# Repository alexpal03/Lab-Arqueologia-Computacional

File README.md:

# Lab-Arqueologia-Computacional

Repositorio dedicado a recopilar información y registrar avances sobre retrocomputadoras del Laboratorio de Arqueología Computacional

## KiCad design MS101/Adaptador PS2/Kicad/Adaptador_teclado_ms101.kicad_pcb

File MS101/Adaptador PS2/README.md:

# Interfaz de Teclado PS/2 a Protocolo Paralelo Microsistemas

Este proyecto implementa un conversor de hardware y software diseñado para leer eventos de un teclado estándar PS/2, interpretarlos, y traducirlos a un bus de datos paralelo de 8 bits propietario (estándar "Microsistemas"). 

El sistema gestiona la recepción asíncrona por interrupciones, decodifica los *scancodes* (incluyendo el estado de modificadores como Shift y Bloq Mayús), los traduce al estándar ASCII, y finalmente mapea dicho ASCII a la codificación binaria requerida por el hardware de destino.

## Nota:
Las teclas de funciones especiales y los shift no fueron nunca probados. Se presupone que el código funcionará. En todo caso, se debería preparar una disquetera para la MS101, correrle el sistema operativo, y luego probar que todas las funcionalidades se ejecuten correctamente.

---

## 🏗️ Arquitectura del Sistema

El flujo de procesamiento se divide en tres etapas principales:

1. **Capa Física (PS/2):** Lectura del protocolo serie síncrono mediante interrupciones de hardware.
2. **Capa Lógica (Máquina de estados):** Filtrado de *scancodes*, manejo de liberación de teclas (`0xF0`) y modificadores.
3. **Capa de Traducción (Pipeline):** `Scancode -> ASCII -> Binario Microsistemas -> Salida Paralela`.

---

## ⚡ 1. Protocolo PS/2 y Recepción por Hardware

El teclado PS/2 se comunica mediante dos líneas en configuración *Open-Drain* (Reloj y Datos). El microcontrolador actúa como receptor pasivo.

### Rutina de Interrupción (ISR)
La recepción se maneja en la función `PS2Interrupt()`, la cual está anclada al flanco de bajada (`FALLING`) del pin de reloj (`PS2_CLK`). 
El protocolo PS/2 envía tramas de **11 bits** por cada evento de teclado:
*   **1 bit de inicio** (siempre 0).
*   **8 bits de datos** (el *Scancode*, LSB primero).
*   **1 bit de paridad** (impar).
*   **1 bit de parada** (siempre 1).

La ISR ignora los bits de inicio, paridad y parada. Desplaza los 8 bits útiles hacia la variable `scancodeRecibido` usando bitwise (`scancodeRecibido |= (dataBit << (bitCount - 1))`). Al alcanzar los 11 bits, levanta la bandera `teclaLista` para cederle el control al bucle principal sin bloquear el procesador.

---

## 🧠 2. Procesamiento Lógico (Bucle Principal)

El `loop()` evalúa la bandera `teclaLista`. Si hay un scancode listo, pasa por una máquina de estados para determinar la acción correcta:

*   **Key Release (0xF0):** Los teclados PS/2 envían `0xF0` seguido del scancode de la tecla cuando esta se suelta. El código enciende la bandera `ignorarSiguienteByte` para no imprimir la letra dos veces. Si la tecla soltada es *Shift* (`0x12` o `0x59`), apaga la bandera `shiftPresionado`.
*   **Modificadores:** Si se presiona *Shift*, se enciende su bandera. Si se presiona *Bloq Mayús* (`0x58`), se invierte el estado booleano de `bloqMayuscActivado`.
*   **Gestión de Mayúsculas/Minúsculas:** Si se presiona una letra y el Bloq Mayús está activo, el sistema aplica aritmética de caracteres C++ (`ascii - 'a' + 'A'`) para invertir el *case* dinámicamente antes de la traducción final.

---

## 🔄 3. Pipeline de Tablas de Conversión

Una vez que se obtiene una tecla válida, atraviesa dos diccionarios de conversión:

1. **`SCANCODE_TO_ASCII_TABLE` (y versión Shifted):** Utiliza la estructura `std::map` para traducir el valor crudo del teclado a un código ASCII. Las teclas de función (F1-F11) están mapeadas intencionalmente a caracteres de control ASCII (0-31) no imprimibles (ej. F1 mapea a `US` [31]).
2. **`ASCII_TO_MICROSISTEMAS_TABLE`:** Es un *array* de 128 posiciones. Usa el valor ASCII obtenido como índice de acceso directo `[ascii]` (O(1)) para recuperar el byte final. 

El mapeo de Microsistemas tiene una estructura semántica en sus bits más significativos (MSB):
*   Los números inician con `0b10...`
*   Las mayúsculas inician con `0b11...`
*   Las minúsculas inician con `0b01...`

---

## 🔌 4. Salida de Hardware (Bus Paralelo)

El byte resultante (`codigoMicrosistemas`) se escribe en los pines GPIO. 
Se utiliza una máscara de bits `(codigoMicrosistemas & (1 << i))` dentro de un bucle `for` de 8 iteraciones para encender o apagar los pines definidos en el arreglo `DATA_PINS`.

Finalmente, se envía un pulso de validación (*Strobe*):
1.  Se levanta el pin `STB_PIN` a `HIGH`.
2.  Se aplica un retardo de `100 microsegundos` para cumplir con los tiempos de *setup/hold* del receptor.
3.  Se baja a `LOW`.

---

## 📊 Tabla de Mapeo Completa: Scancode a Microsistemas

A continuación se detalla el recorrido exacto de transformación de cada tecla, número y función desde el teclado físico hasta la salida binaria de 8 bits.

### 🔢 Números
| Scancode PS/2 (Hex) | ASCII Base (Char / Valor) | Tecla Microsistemas | Salida Binaria Microsistemas |
| :--- | :--- | :--- | :--- |
| **0x45** | `'0'` (48) | Número 0 | `0b10100000` |
| **0x16** | `'1'` (49) | Número 1 | `0b10100001` |
| **0x1E** | `'2'` (50) | Número 2 | `0b10100010` |
| **0x26** | `'3'` (51) | Número 3 | `0b10100011` |
| **0x25** | `'4'` (52) | Número 4 | `0b10100100` |
| **0x2E** | `'5'` (53) | Número 5 | `0b10100101` |
| **0x36** | `'6'` (54) | Número 6 | `0b10100110` |
| **0x3D** | `'7'` (55) | Número 7 | `0b10100111` |
| **0x3E** | `'8'` (56) | Número 8 | `0b10101000` |
| **0x46** | `'9'` (57) | Número 9 | `0b10101001` |

### 🔤 Letras Minúsculas
| Scancode PS/2 (Hex) | ASCII Base (Char / Valor) | Tecla Microsistemas | Salida Binaria Microsistemas |
| :--- | :--- | :--- | :--- |
| **0x1C** | `'a'` (97) | Letra a | `0b01110100` |
| **0x32** | `'b'` (98) | Letra b | `0b01111011` |
| **0x21** | `'c'` (99) | Letra c | `0b01111100` |
| **0x23** | `'d'` (100)| Letra d | `0b01111101` |
| **0x24** | `'e'` (101)| Letra e | `0b01111110` |
| **0x2B** | `'f'` (102)| Letra f | `0b01111111` |
| **0x34** | `'g'` (103)| Letra g | `0b01010110` |
| **0x33** | `'h'` (104)| Letra h | `0b01010111` |
| **0x43** | `'i'` (105)| Letra i | `0b01100010` |
| **0x3B** | `'j'` (106)| Letra j | `0b01100100` |
| **0x42** | `'k'` (107)| Letra k | `0b01100101` |
| **0x4B** | `'l'` (108)| Letra l | `0b01100110` |
| **0x3A** | `'m'` (109)| Letra m | `0b01100111` |
| **0x31** | `'n'` (110)| Letra n | `0b01011011` |
| **0x44** | `'o'` (111)| Letra o | `0b01100011` |
| **0x4D** | `'p'` (112)| Letra p | `0b01010100` |
| **0x15** | `'q'` (113)| Letra q | `0b01101010` |
| **0x2D** | `'r'` (114)| Letra r | `0b01010001` |
| **0x1B** | `'s'` (115)| Letra s | `0b01010101` |
| **0x2C** | `'t'` (116)| Letra t | `0b01010010` |
| **0x3C** | `'u'` (117)| Letra u | `0b01100001` |
| **0x2A** | `'v'` (118)| Letra v | `0b01011010` |
| **0x1D** | `'w'` (119)| Letra w | `0b01010000` |
| **0x22** | `'x'` (120)| Letra x | `0b01011001` |
| **0x35** | `'y'` (121)| Letra y | `0b01010011` |
| **0x1A** | `'z'` (122)| Letra z | `0b01011000` |

### 🅰️ Letras Mayúsculas (Requieren Modificador Shift / Bloq Mayús)
| Scancode PS/2 (Hex) | ASCII Shifted (Char / Valor) | Tecla Microsistemas | Salida Binaria Microsistemas |
| :--- | :--- | :--- | :--- |
| **0x1C** *(+ Shift)* | `'A'` (65) | Letra A | `0b11110100` |
| **0x32** *(+ Shift)* | `'B'` (66) | Letra B | `0b11111011` |
| **0x21** *(+ Shift)* | `'C'` (67) | Letra C | `0b11111100` |
| **0x23** *(+ Shift)* | `'D'` (68) | Letra D | `0b11111101` |
| **0x24** *(+ Shift)* | `'E'` (69) | Letra E | `0b11111110` |
| **0x2B** *(+ Shift)* | `'F'` (70) | Letra F | `0b11111111` |
| **0x34** *(+ Shift)* | `'G'` (71) | Letra G | `0b11010110` |
| **0x33** *(+ Shift)* | `'H'` (72) | Letra H | `0b11010111` |
| **0x43** *(+ Shift)* | `'I'` (73) | Letra I | `0b11100010` |
| **0x3B** *(+ Shift)* | `'J'` (74) | Letra J | `0b11100100` |
| **0x42** *(+ Shift)* | `'K'` (75) | Letra K | `0b11100101` |
| **0x4B** *(+ Shift)* | `'L'` (76) | Letra L | `0b11100110` |
| **0x3A** *(+ Shift)* | `'M'` (77) | Letra M | `0b11100111` |
| **0x31** *(+ Shift)* | `'N'` (78) | Letra N | `0b11011011` |
| **0x44** *(+ Shift)* | `'O'` (79) | Letra O | `0b11100011` |
| **0x4D** *(+ Shift)* | `'P'` (80) | Letra P | `0b11010100` |
| **0x15** *(+ Shift)* | `'Q'` (81) | Letra Q | `0b11101010` |
| **0x2D** *(+ Shift)* | `'R'` (82) | Letra R | `0b11010001` |
| **0x1B** *(+ Shift)* | `'S'` (83) | Letra S | `0b11010101` |
| **0x2C** *(+ Shift)* | `'T'` (84) | Letra T | `0b11010010` |
| **0x3C** *(+ Shift)* | `'U'` (85) | Letra U | `0b11100001` |
| **0x2A** *(+ Shift)* | `'V'` (86) | Letra V | `0b11011010` |
| **0x1D** *(+ Shift)* | `'W'` (87) | Letra W | `0b11010000` |
| **0x22** *(+ Shift)* | `'X'` (88) | Letra X | `0b11011001` |
| **0x35** *(+ Shift)* | `'Y'` (89) | Letra Y | `0b11010011` |
| **0x1A** *(+ Shift)* | `'Z'` (90) | Letra Z | `0b11011000` |

### 🛠️ Teclas de Control y Sistema
| Scancode PS/2 (Hex) | ASCII Base (Char / Valor) | Tecla / Acción Microsistemas | Salida Binaria Microsistemas |
| :--- | :--- | :--- | :--- |
| **0x29** | `SPACE` (32) | Espacio | `0b11011111` |
| **0x5A** (Enter) | `ETX` (3) | **SKIP** | `0b11011100` |
| **0x66** (Backspace) | `BS` (8) | **RESET** | `0b11110010` |
| **0x0D** (Tab)| `HT` (9) | **RIGHT ADJUST** | `0b11110101` |
| **0x76** (Escape)| `ESC` (27) | **NEW LINE** | `0b11110110` |
| **0x0A** (F8)| `DEL` (127) | **FIELD COR** | `0b11001000` |
| **0x05** (F1)| `US` (31) | **CHR BCK** | `0b11011110` |
| **0x06** (F2)| `GS` (29) | **FIELD BCK** | `0b11110000` |
| **0x04** (F3)| `RS` (30) | **REC BCK** | `0b11111000` |
| **0x0C** (F4)| `DC1` (17) | **CHR ADV** | `0b11001010` |
| **0x03** (F5)| `DC2` (18) | **FIELD ADV** | `0b11001100` |
| **0x0B** (F6)| `DC3` (19) | **REC ADV** | `0b11101100` |
| **0x83** (F7)| `BEL` (7) | **HEX** | `0b11000011` |
| **0x83** (F9)| `LF` (10) | **FUNC SEL** | `0b11000001` |
| **0x83** (F10)| `VT` (11) | **DUP** | `0b11001001` |
| **0x83** (F11)| `FF` (12) | **SEL PROG** | `0b11001101` |

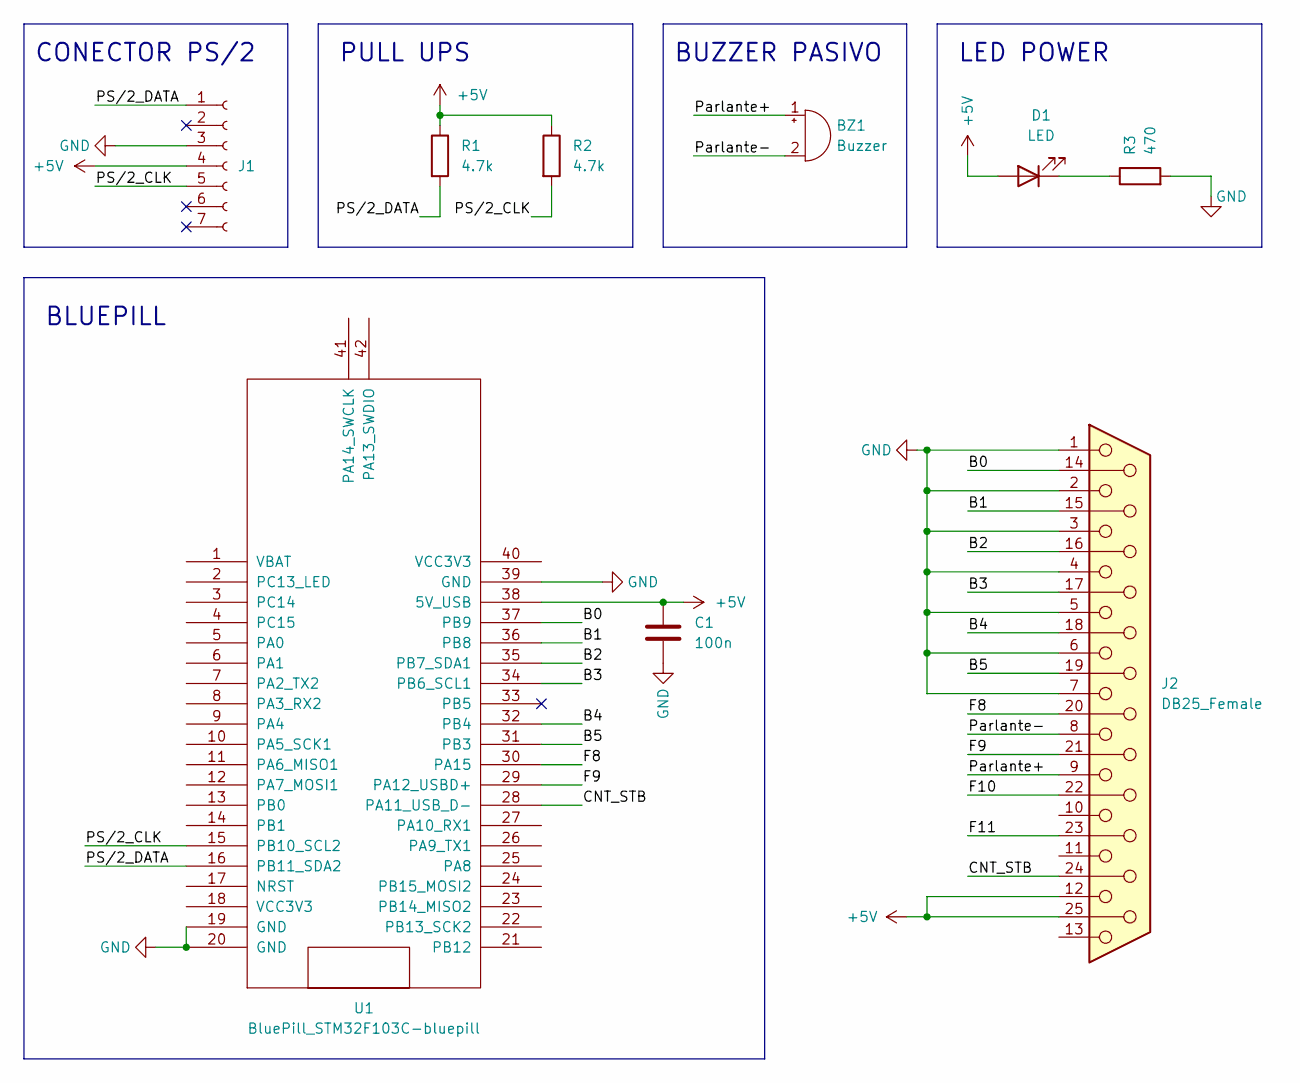
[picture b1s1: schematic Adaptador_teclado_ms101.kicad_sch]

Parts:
BZ1: Buzzer; Buzzer_12x9.5RM7.6
C1: 100n; C_Disc_D5.0mm_W2.5mm_P5.00mm
D1: LED; LED_D5.0mm
J1: Conn_01x07_Female; Connector_Mini-DIN_Female_6Pin_2rows
J2: DB25_Female; DSUB-25_Female_EdgeMount_P2.77mm
R1, R2: 4.7k; R_Axial_DIN0309_L9.0mm_D3.2mm_P12.70mm_Horizontal
R3: 470; R_Axial_DIN0309_L9.0mm_D3.2mm_P12.70mm_Horizontal
U1: BluePill_STM32F103C-bluepill; Bluepill

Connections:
+5V: C1.1, D1.2 (A), J1.4, J2.12, J2.25, R1.1, R2.1, U1.38 (5V_USB)
/B0: J2.14, U1.37 (PB9)
/B1: J2.15, U1.36 (PB8)
/B2: J2.16, U1.35 (PB7_SDA1)
/B3: J2.17, U1.34 (PB6_SCL1)
/B4: J2.18, U1.32 (PB4)
/B5: J2.19, U1.31 (PB3)
/CNT_STB: J2.24, U1.28 (PA11_USB_D-)
/F8: J2.20, U1.30 (PA15)
/F9: J2.21, U1.29 (PA12_USBD+)
/F10: J2.22
/F11: J2.23
/PS/2_CLK: J1.5, R2.2, U1.15 (PB10_SCL2)
/PS/2_DATA: J1.1, R1.2, U1.16 (PB11_SDA2)
/Parlante+: BZ1.1 (-), J2.9
/Parlante-: BZ1.2 (+), J2.8
GND: C1.2, J1.3, J2.1, J2.2, J2.3, J2.4, J2.5, J2.6, J2.7, R3.2, U1.19 (GND), U1.20 (GND), U1.39 (GND)
unnamed: D1.1 (K), R3.1

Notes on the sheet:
LED POWER
CONECTOR PS/2
BLUEPILL
PULL UPS
BUZZER PASIVO

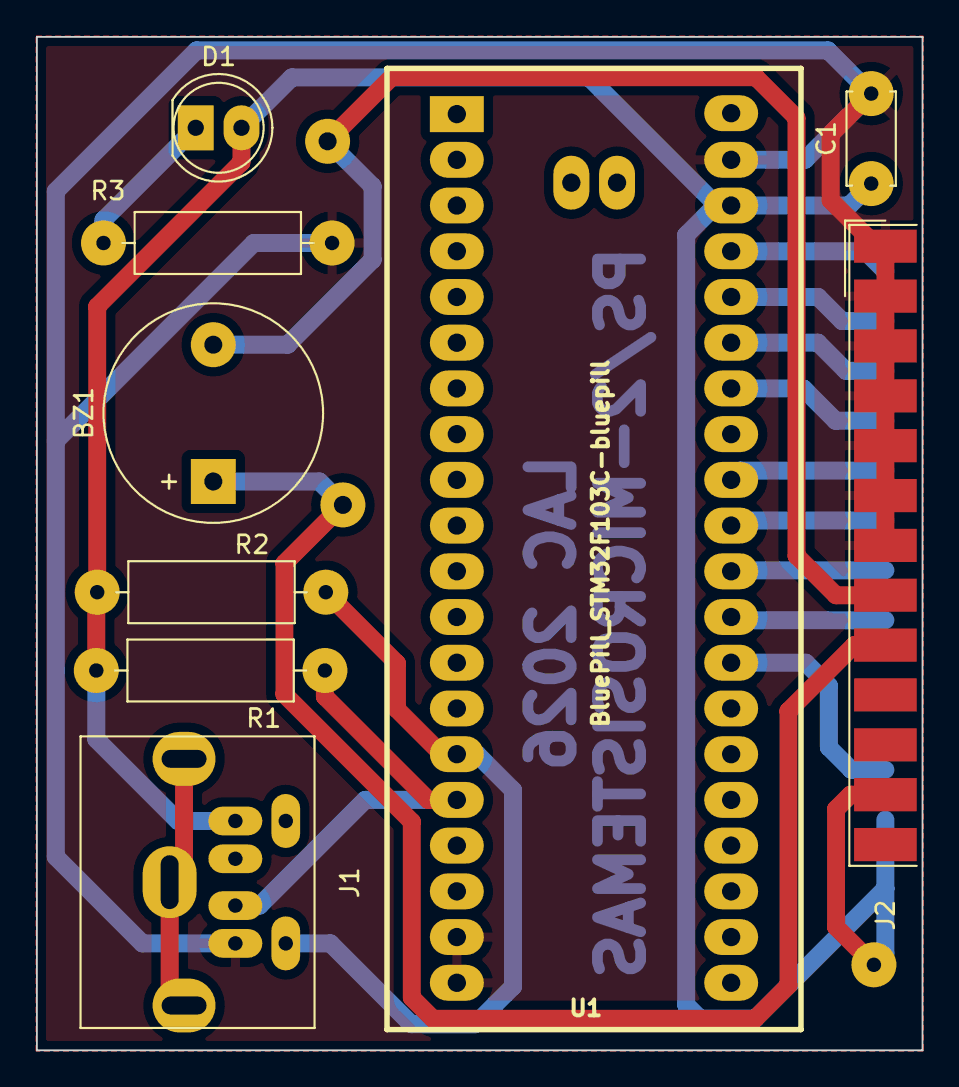
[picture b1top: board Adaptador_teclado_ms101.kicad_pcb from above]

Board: 2 copper layers, 49.2 x 56.3 mm, 9 parts (0 on the bottom side), 16 nets.

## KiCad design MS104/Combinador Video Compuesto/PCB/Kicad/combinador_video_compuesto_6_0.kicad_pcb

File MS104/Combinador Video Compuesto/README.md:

# Combinador Video Compuesto

## Principio de funcionamiento

La placa de video de las computadoras MS101 y MS104 funcionan generando 3 señales:

* Iluminación (3V)
* (VSYNC) Sincronización vertical de 50Hz (3.8V)
* (HSYNC) Sincronización Horizontal de 15.625Khz (3.65V)

La función de la placa combinadora es la de sumar las 3 señales para generar un video compuesto estandar PAL. Para poder lograrlo no solo hay que modificar las amplitudes de las señales, sino que tambien (en el caso de la sincronización horizontal) había que modificar su ancho de pulso. El objetivo era lograr una señal resultante de 1Vpp, que tenga la siguiente forma

Una parte clave del combinador era lograr que el pulso de HSYNC quede invertido, y con un ancho de pulso de 4.7us. Para ello, se utilizó un circuito RC temporizador que mediante regulación con un trimpot, modificaría la constante tau y permitiría ajustar a un ancho de 4.7us dejando la frecuencia intacta. Una vez conseguido esto, los valores de front porch y back porch se acomodaron solos.

Por otro lado, para el control del vertical, en el video compuesto tradicional se sustituye cada 20ms (50Hz) el pulso HSYNC por un pulso más largo, indicando que es momento de sincronizar el vertical. Esta sustitución se puede lograr mediante una operación lógica de AND entre el pulso horizontal y vertical. A esta señal resultante de la operación HSYNC & VSYNC se la conoce como CSYNC (Sincronización compuesta)

Una vez conseguido esto, solo es necesario sumar la señal CSYNC con la iluminación para obtener el video compuesto. La iluminación debe quedar con 0.7Vpp y el CSYNC con 0.3Vpp. Cabe aclarar que el transistor que se ocupa de realizar esta última suma debe ser un transistor de alta frecuencia, de lo contrario la señal de iluminación puede verse alterada. En esta placa se utilizó el [KPS10](https://www.alldatasheet.es/datasheet-pdf/pdf/53500/FAIRCHILD/KSP10.html)

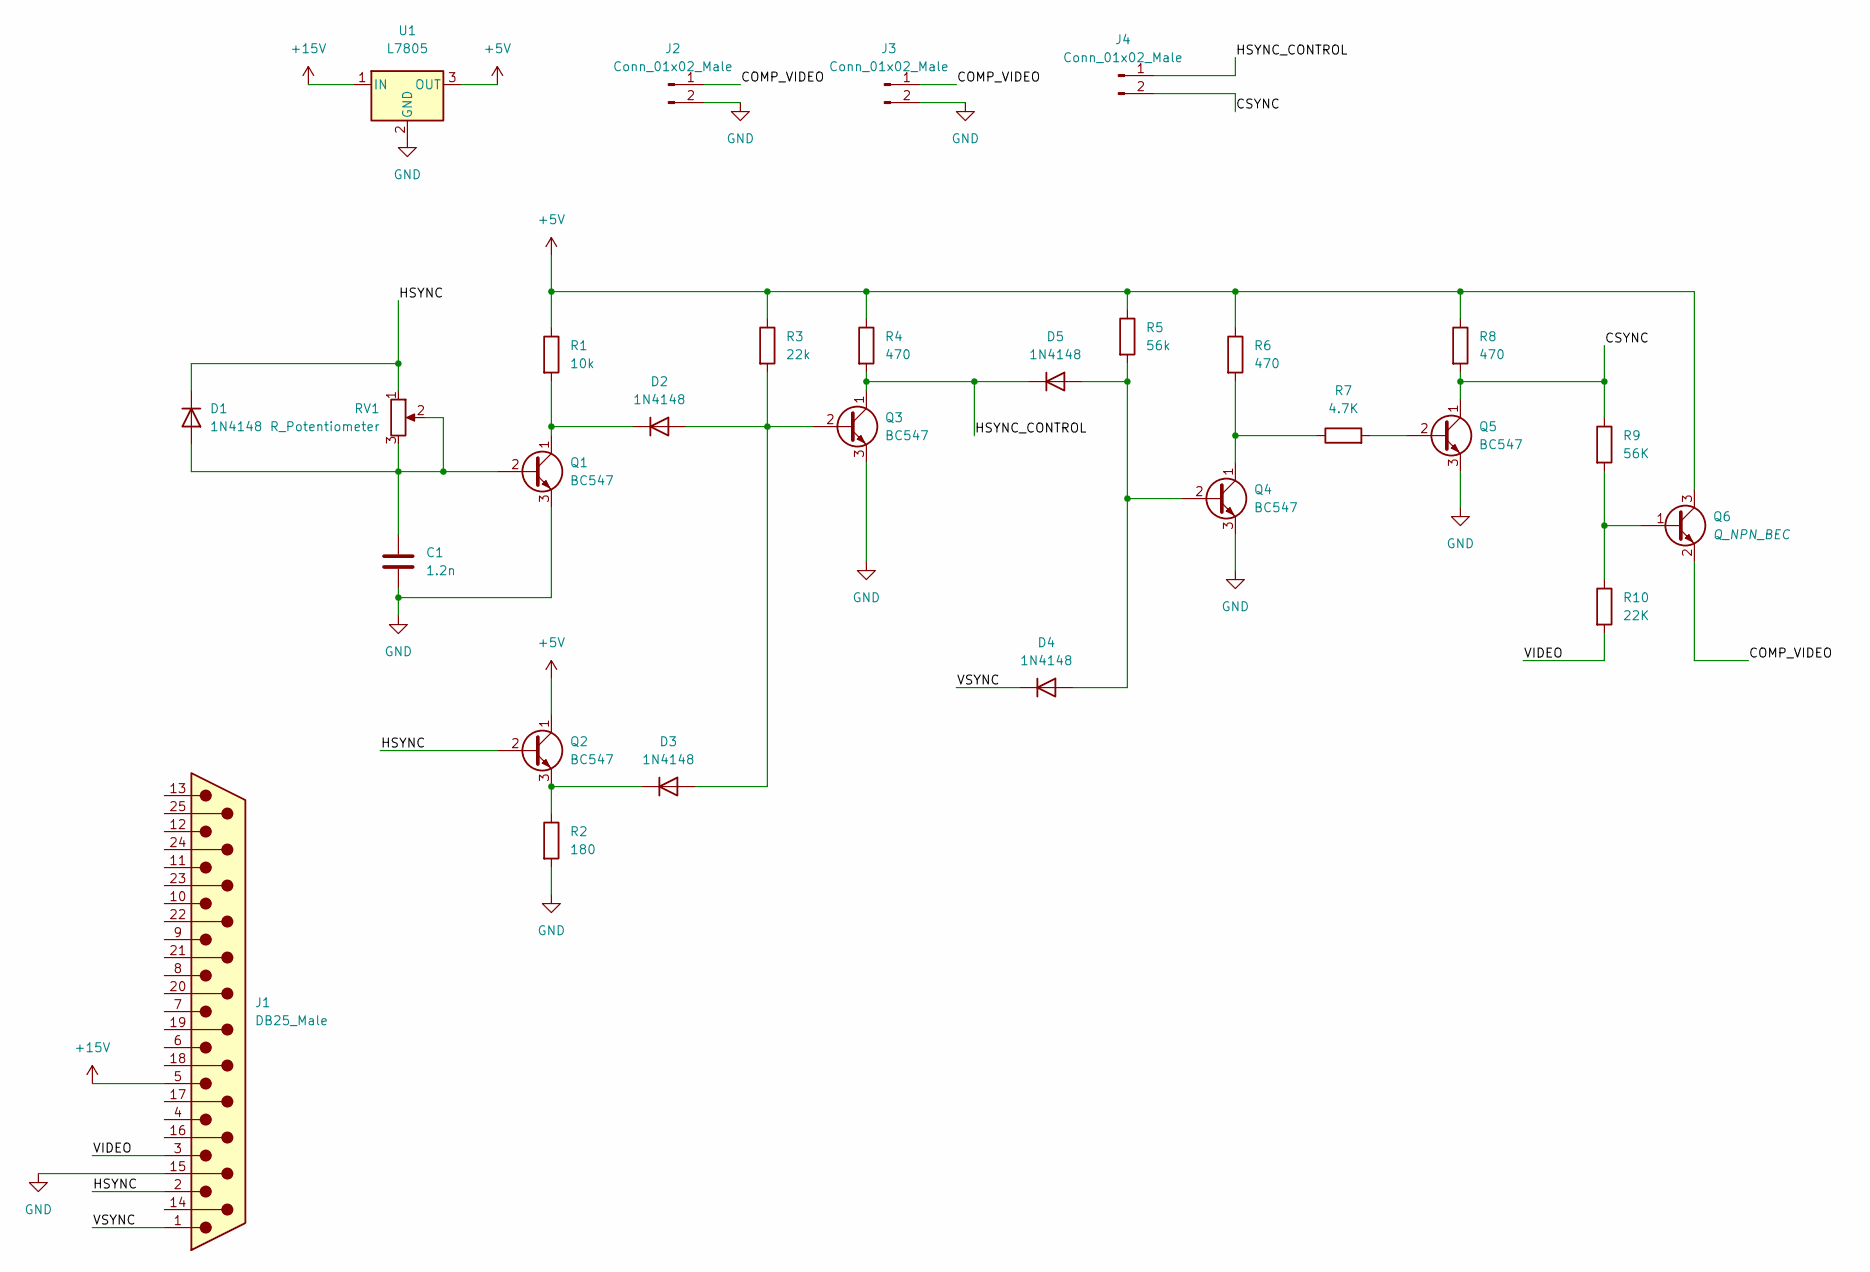
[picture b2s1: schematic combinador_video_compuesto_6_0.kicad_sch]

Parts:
C1: 1.2n; C_Disc_D7.5mm_W5.0mm_P5.00mm
D1, D2, D3, D4, D5: 1N4148; D_DO-35_SOD27_P7.62mm_Horizontal
J1: DB25_Male; DSUB-25_Male_EdgeMount_P2.77mm
J2: Conn_01x02_Male; PinHeader_1x02_P2.54mm_Horizontal
J3: Conn_01x02_Male; BNC_Amphenol_B6252HB-NPP3G-50_Horizontal
J4: Conn_01x02_Male; PinHeader_1x02_P2.54mm_Vertical
Q1, Q2, Q3, Q4, Q5: BC547; TO-92_Wide
Q6: Q_NPN_BEC; TO-92_Wide
R1: 10k; R_Axial_DIN0411_L9.9mm_D3.6mm_P12.70mm_Horizontal
R2: 180; R_Axial_DIN0411_L9.9mm_D3.6mm_P12.70mm_Horizontal
R3: 22k; R_Axial_DIN0411_L9.9mm_D3.6mm_P12.70mm_Horizontal
R4, R6, R8: 470; R_Axial_DIN0411_L9.9mm_D3.6mm_P12.70mm_Horizontal
R5: 56k; R_Axial_DIN0411_L9.9mm_D3.6mm_P12.70mm_Horizontal
R7: 4.7K; R_Axial_DIN0411_L9.9mm_D3.6mm_P12.70mm_Horizontal
R9: 56K; R_Axial_DIN0411_L9.9mm_D3.6mm_P12.70mm_Horizontal
R10: 22K; R_Axial_DIN0411_L9.9mm_D3.6mm_P12.70mm_Horizontal
RV1: R_Potentiometer; Potentiometer_Bourns_3006P_Horizontal
U1: L7805; TO-220-3_Vertical

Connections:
+5V: Q2.1 (C), Q6.3 (C), R1.1, R3.1, R4.1, R5.1, R6.1, R8.1, U1.3 (OUT)
+15V: J1.5, U1.1 (IN)
/COMP_VIDEO: J2.1, J3.1, Q6.2 (E)
/CSYNC: J4.2, Q5.1 (C), R8.2, R9.1
/HSYNC: D1.1 (K), J1.2, Q2.2 (B), RV1.1
/HSYNC_CONTROL: D5.1 (K), J4.1, Q3.1 (C), R4.2
/VIDEO: J1.3, R10.2
/VSYNC: D4.1 (K), J1.1
GND: C1.2, J1.15, J2.2, J3.2, Q1.3 (E), Q3.3 (E), Q4.3 (E), Q5.3 (E), R2.2, U1.2 (GND)
unnamed: C1.1, D1.2 (A), Q1.2 (B), RV1.2, RV1.3
unnamed: D2.1 (K), Q1.1 (C), R1.2
unnamed: D2.2 (A), D3.2 (A), Q3.2 (B), R3.2
unnamed: D3.1 (K), Q2.3 (E), R2.1
unnamed: D4.2 (A), D5.2 (A), Q4.2 (B), R5.2
unnamed: Q4.1 (C), R6.2, R7.1
unnamed: Q5.2 (B), R7.2
unnamed: Q6.1 (B), R9.2, R10.1

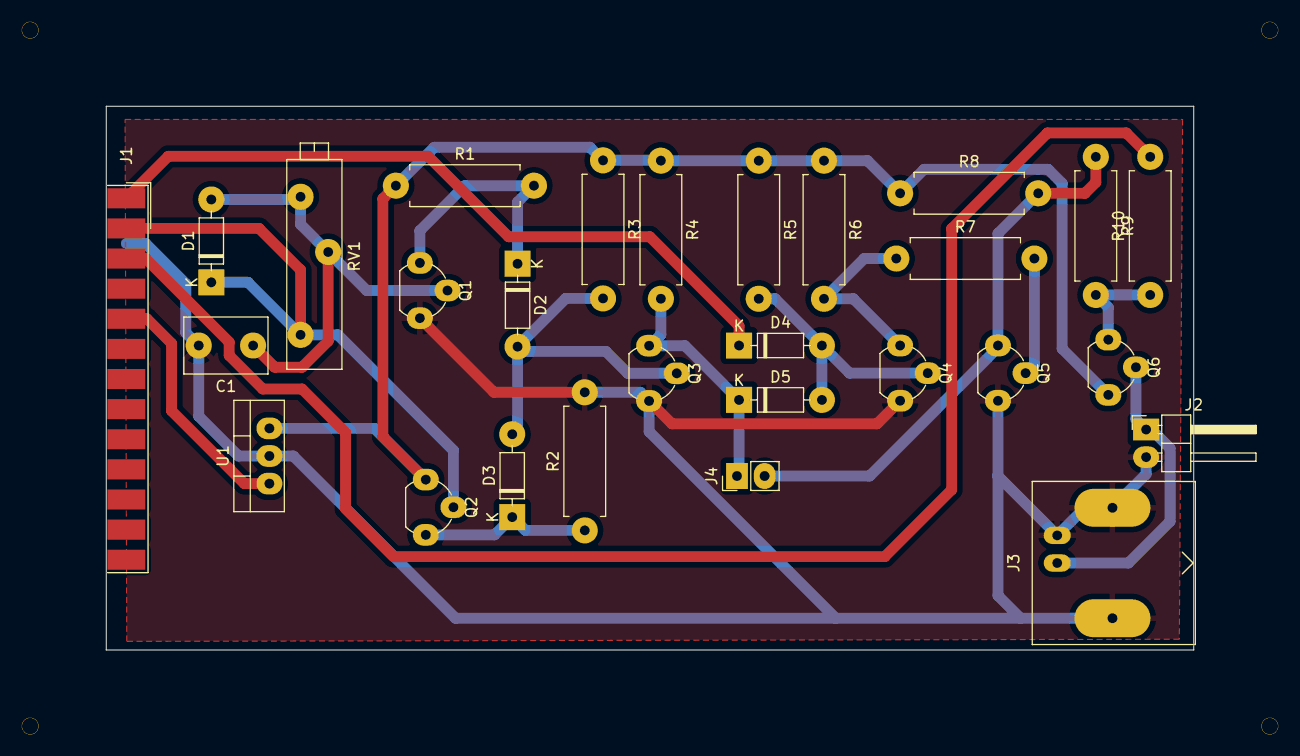
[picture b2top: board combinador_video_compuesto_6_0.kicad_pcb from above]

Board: 2 copper layers, 100.0 x 50.0 mm, 28 parts (0 on the bottom side), 17 nets.

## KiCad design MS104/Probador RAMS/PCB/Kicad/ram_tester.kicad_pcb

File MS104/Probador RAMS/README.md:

# Probador de RAM de 64kbytes para MS101 - MS104

El probador tiene capacidad de verificar hasta 64kbytes de memoria RAM, pero lo hace por sectores conformados por 8kbytes.
En total hay 8 sectores.

La decisión de usar esta delimitación de sectores es debido al mapeo de memoria de la 101-104:

|Sector| Direcciones |
| ---- | --------- |
|  I   |0000 - 1FFF|
|  II (A)   |2000 - 3FFF|
| III (B)  |4000 - 5FFF|
|  IV   |6000 - 7FFF|
|  V (C)  |8000 - 9FFF|
|  VI   |A000 - BFFF|
|  VII   |C000 - DFFF|
|  VIII (D)  |E000 - FFFF|

## Modo de uso

1. Conectar el probador de ram en el algún espacio del rack de tarjetas, preferiblemene en el espacio del CPU. Desconectar todas las demás placas, menos la tarjeta RAM
2. Hacer doble click en el botón para entrar a la configuración, donde se podrá seleccionar el sector a testear. Para moverse por las opciones se debe hacer un solo click, y una vez que se seleccione el sector deseado se vuelve a presionar doble click para volver al inicio.
3. Una vez en el inicio, se comienza el test con un solo click.
4. Al finalizar el test, aparece la primera pantalla de resultado, que indica la cantidad de direcciones donde hubo errores de lectura. Con un click se pasa a la siguiente pantalla, donde se muestra con mayor detalle los bits que tuvieron fallas organizados en bloques de 1kbyte. Ejemplo:

    ```
    7F 00 00 00
    00 50 00 00
    ```
    El `7F` que en binario es `01111111`, significa que en el primer bloque de 1kbyte fallaron todos los bits a excepción del más significativo.
    El `50` que en binario es `01010000` significa que en el sexto bloque de 1kbyte solo hay fallas en el B6 y B4.

    Esta subdivisión es útil porque tanto los integrados de RAM de la 101 y la 104 son de 1024 direcciones. De esta forma se puede localizar mucho más fácil la falla. Ej: si todos los bloques de 1kbyte fallan en el mismo bit, es probable que la falla sea del buffer de datos, y no de las RAM.

   A continuación se muestra un mapa de memoria de la MS104 y como se deben interpŕetar los resultados en el mapa

[Con mas detalle en este link](https://github.com/alexpal03/Lab-Arqueologia-Computacional/blob/main/MS104/Probador%20RAMS/Lectura%20de%20resultados.pdf)

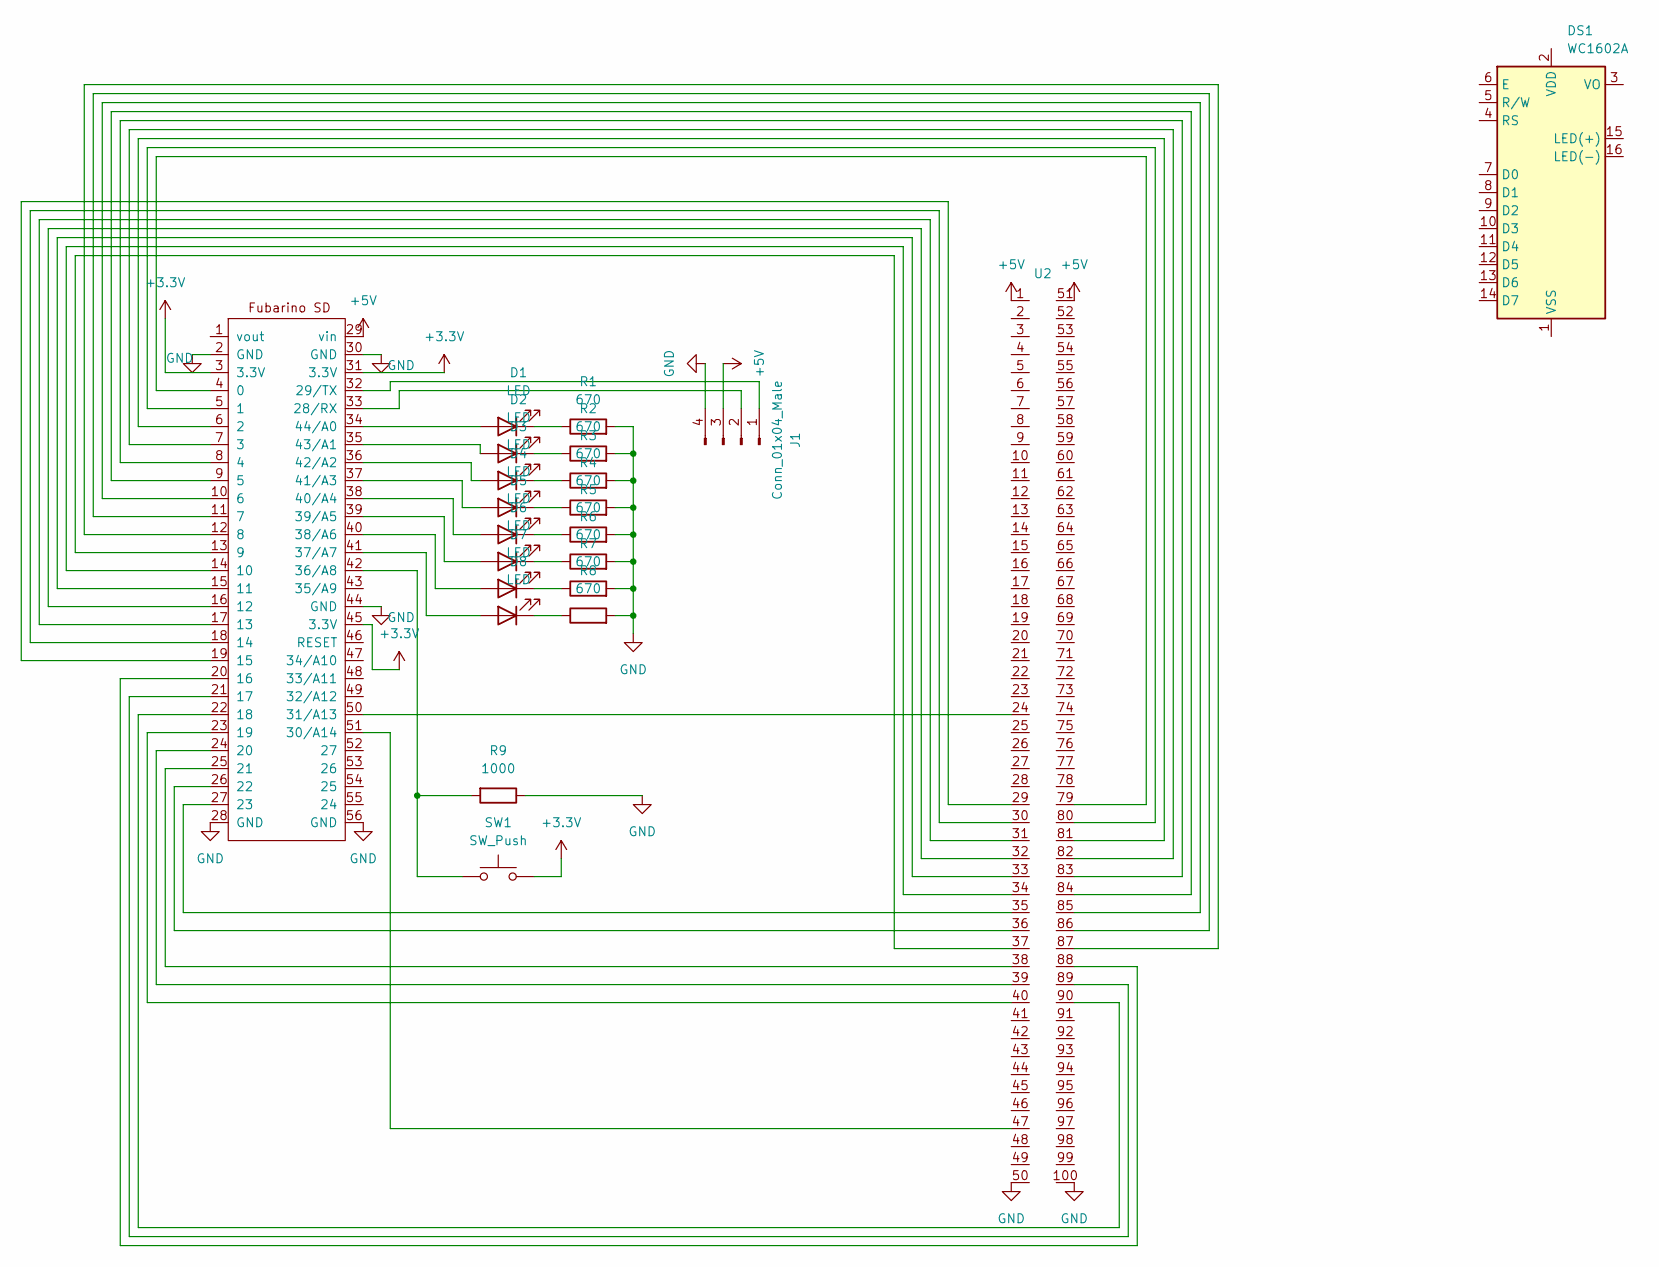
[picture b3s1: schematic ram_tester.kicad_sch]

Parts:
D1, D2, D3, D4, D5, D6, D7, D8: LED; LED_D3.0mm_Horizontal_O6.35mm_Z10.0mm
DS1: WC1602A
J1: Conn_01x04_Male; PinSocket_1x04_P2.54mm_Horizontal
R1, R2, R3, R4, R5, R6, R7, R8: 670; R_Axial_DIN0207_L6.3mm_D2.5mm_P10.16mm_Horizontal
R9: 1000; R_Axial_DIN0207_L6.3mm_D2.5mm_P10.16mm_Horizontal
SW1: SW_Push; SW_PUSH_6mm_H5mm
U1: fubarino_sd
U2: s100

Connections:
+3.3V: SW1.2, U1.3 (3.3V), U1.31 (3.3V), U1.45 (3.3V)
+5V: J1.3, U1.29 (vin), U2.1, U2.51
GND: J1.4, R1.2, R2.2, R3.2, R4.2, R5.2, R6.2, R7.2, R8.2, R9.1, U1.2 (GND), U1.28 (GND), U1.30 (GND), U1.44 (GND), U1.56 (GND), U2.50, U2.100
unnamed: D1.2 (A), U1.34 (44/A0)
unnamed: D1.1 (K), R1.1
unnamed: D2.2 (A), U1.35 (43/A1)
unnamed: D2.1 (K), R2.1
unnamed: D3.2 (A), U1.36 (42/A2)
unnamed: D3.1 (K), R3.1
unnamed: D4.2 (A), U1.37 (41/A3)
unnamed: D4.1 (K), R4.1
unnamed: D5.2 (A), U1.38 (40/A4)
unnamed: D5.1 (K), R5.1
unnamed: D6.2 (A), U1.39 (39/A5)
unnamed: D6.1 (K), R6.1
unnamed: D7.2 (A), U1.40 (38/A6)
unnamed: D7.1 (K), R7.1
unnamed: D8.2 (A), U1.41 (37/A7)
unnamed: D8.1 (K), R8.1
unnamed: J1.1, U1.32 (29/TX)
unnamed: J1.2, U1.33 (28/RX)
unnamed: U1.4 (0), U2.79
unnamed: U1.5 (1), U2.80
unnamed: U1.6 (2), U2.81
unnamed: U1.7 (3), U2.82
unnamed: U1.8 (4), U2.83
unnamed: U1.9 (5), U2.84
unnamed: U1.10 (6), U2.85
unnamed: U1.11 (7), U2.86
unnamed: U1.12 (8), U2.87
unnamed: U1.13 (9), U2.37
unnamed: U1.14 (10), U2.34
unnamed: U1.15 (11), U2.33
unnamed: U1.16 (12), U2.32
unnamed: U1.17 (13), U2.31
unnamed: U1.18 (14), U2.30
unnamed: U1.19 (15), U2.29
unnamed: U1.20 (16), U2.88
unnamed: U1.21 (17), U2.89
unnamed: U1.22 (18), U2.90
unnamed: U1.23 (19), U2.40
unnamed: U1.24 (20), U2.39
unnamed: U1.25 (21), U2.38
unnamed: U1.26 (22), U2.36
unnamed: U1.27 (23), U2.35
unnamed: U1.51 (30/A14), U2.47
unnamed: U1.50 (31/A13), U2.24
unnamed: R9.2, SW1.1, U1.42 (36/A8)

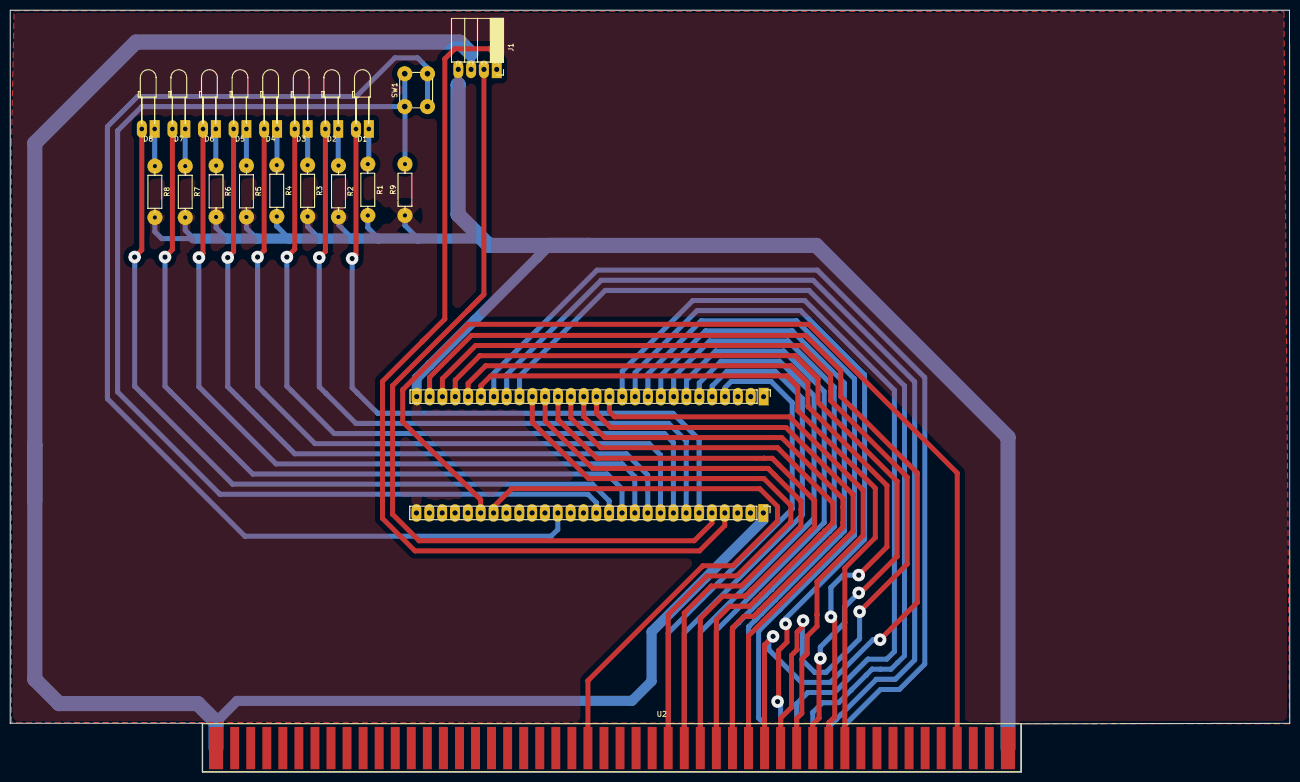
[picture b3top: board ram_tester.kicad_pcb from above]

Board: 2 copper layers, 253.0 x 150.6 mm, 21 parts (0 on the bottom side), 48 nets.

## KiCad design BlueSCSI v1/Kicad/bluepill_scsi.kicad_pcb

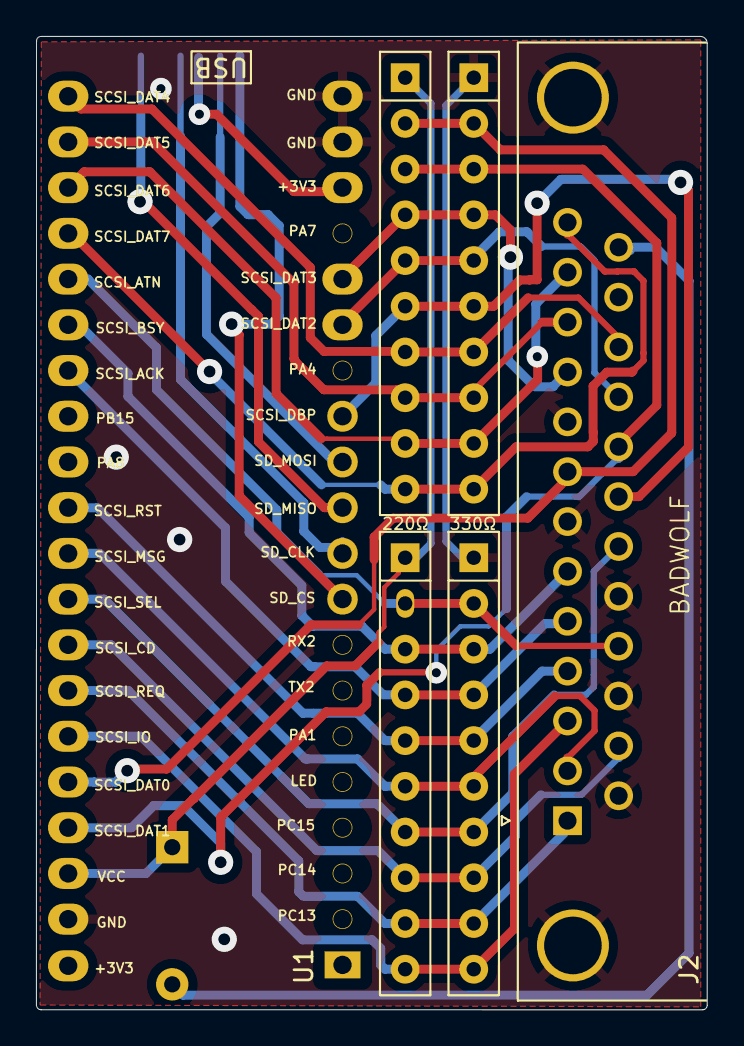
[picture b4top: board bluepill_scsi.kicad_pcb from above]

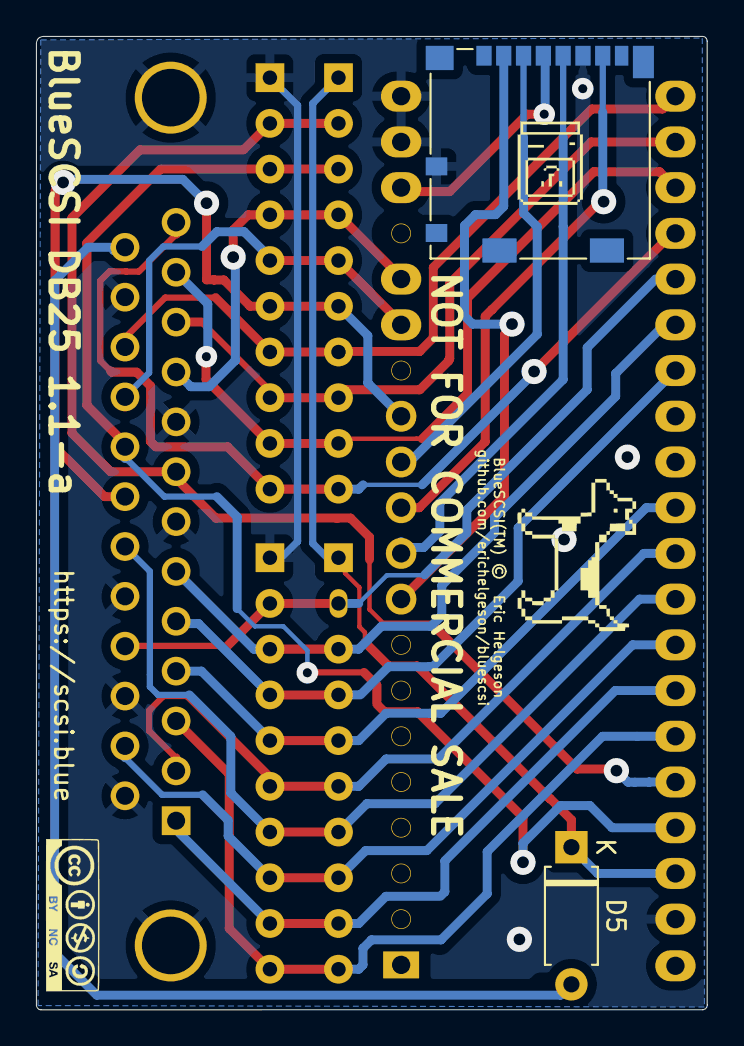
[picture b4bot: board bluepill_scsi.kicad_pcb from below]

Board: 2 copper layers, 37.3 x 54.1 mm, 11 parts (5 on the bottom side), 26 nets.

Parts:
D5: Diode; D_A-405_P7.62mm_Horizontal
G001: LOGO; dogcow
G002: LOGO; cc_by_nc_sa_front_silk_screen
G004: LOGO; mac_happy_small
J2: DB25_Male_MountingHoles; DSUB-25_Male_Horizontal_P2.77x2.84mm_EdgePinOffset4.94mm_Ho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
J5: Micro_SD_Card; microSD_HC_Molex_104031-0811
RN1, RN3: 220; R_Array_SIP10
RN2, RN4: 330; R_Array_SIP10
U1: BluePill_STM32F103C

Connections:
+3V3: J5.4, U1.18, U1.40
/SCSI_ACK: J2.5, RN3.4, RN4.4, U1.27
/SCSI_ATN: J2.17, RN3.2, RN4.2, U1.25
/SCSI_BSY: J2.6, RN3.3, RN4.3, U1.26
/SCSI_CD: J2.15, RN3.8, RN4.8, U1.33
/SCSI_DAT0: J2.8, RN1.2, RN2.2, U1.36
/SCSI_DAT1: J2.21, RN1.3, RN2.3, U1.37
/SCSI_DAT2: J2.22, RN1.5, RN2.5, U1.15
/SCSI_DAT3: J2.10, RN1.4, RN2.4, U1.16
/SCSI_DAT4: J2.23, RN1.7, RN2.7, U1.21
/SCSI_DAT5: J2.11, RN1.8, RN2.8, U1.22
/SCSI_DAT6: J2.12, RN1.9, RN2.9, U1.23
/SCSI_DAT7: J2.13, RN1.10, RN2.10, U1.24
/SCSI_DBP: J2.20, RN1.6, RN2.6, U1.13
/SCSI_IO: J2.3, RN3.10, RN4.10, U1.35
/SCSI_MSG: J2.2, RN3.6, RN4.6, U1.31
/SCSI_REQ: J2.1, RN3.9, RN4.9, U1.34
/SCSI_RST: J2.4, RN3.5, RN4.5, U1.30
/SCSI_SEL: J2.19, RN3.7, RN4.7, U1.32
/SD_CLK: J5.5, U1.10
/SD_CS: J5.2, U1.9
/SD_MISO: J5.7, U1.11
/SD_MOSI: J5.3, U1.12
/TERM_PWR: D5.2, J2.25
GND: J2.0, J2.7, J2.9, J2.14, J2.16, J2.18, J2.24, J5.6, J5.9, RN2.1, RN4.1, U1.19, U1.20, U1.39
VCC: D5.1, RN1.1, RN3.1, U1.38

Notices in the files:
BlueSCSI v1/Kicad/bluepill_scsi.kicad_pcb:
BlueSCSI(TM) ©  Eric Helgeson
